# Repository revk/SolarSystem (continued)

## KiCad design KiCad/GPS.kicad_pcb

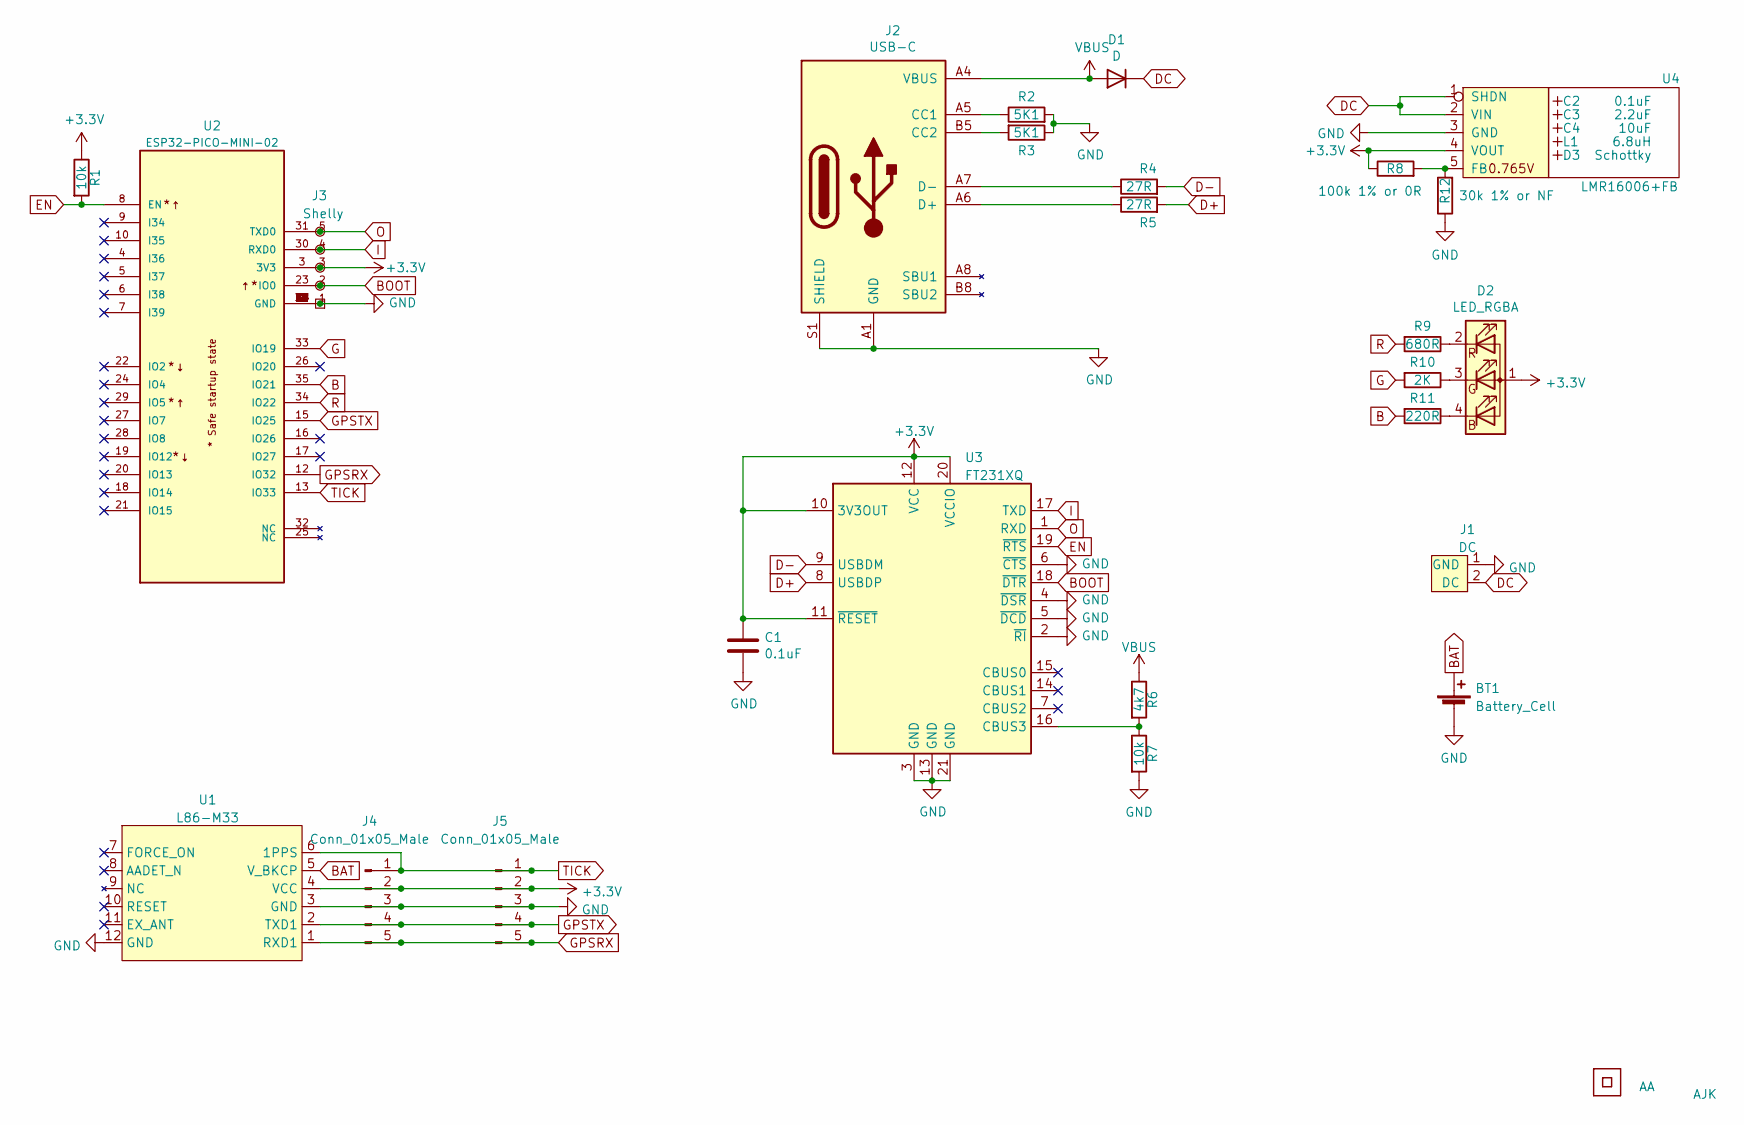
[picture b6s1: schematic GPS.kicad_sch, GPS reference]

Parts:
BT1: Battery_Cell; Battery-Holder-2032
C1: 0.1uF; C_0603
C2: 0.1uF; C_0603_
C3: 2.2uF; C_0805_
C4: 10uF; C_0805_
D1: D; D_1206
D2: LED_RGBA; LED-RGB-1.6x1.6
D3: Schottky; D_1206_; Part No CD1206-B2100
J1: DC; Molex_MiniSPOX_H2RA
J2: USB-C; USC16-TR
J3: Shelly
J4, J5: Conn_01x05_Male; PinHeader_1x05_P1.27mm_Vertical
L1: 6.8uH; L_4x4_; Part No TYA4020
Logo1: AA
Logo2: AJK
R1, R7: 10k; R_0603
R2, R3: 5K1; R_0603
R4, R5: 27R; R_0603
R6: 4k7; R_0603
R8: 100k 1% or 0R; R_0603
R9: 680R; R_0603
R10: 2K; R_0603
R11: 220R; R_0603
R12: 30k 1% or NF; R_0603
U1: L86-M33
U2: ESP32-PICO-MINI-02; PARTREV v1.0
U3: FT231XQ; QFN-20-1EP_4x4mm_P0.5mm_EP2.5x2.5mm
U4: LMR16006+FB; SOT-23-Thin-6-Reg; Part No LMR16006YQ3
U5: QR; QR-SS

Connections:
+3V3: C1.1, D2.1 (A), J3.3 (3V3), J4.2, J5.2, R1.1, R8.1, U1.4 (VCC), U2.3 (3V3), U3.10 (3V3OUT), U3.11 (~RESET), U3.12 (VCC), U3.20 (VCCIO), U4.4 (VOUT)
B: R11.2, U2.35 (IO21)
BAT: BT1.1 (+), U1.5 (V_BKCP)
BOOT: J3.2 (0), U2.23 (IO0), U3.18 (~DTR)
D+: R5.2, U3.8 (USBDP)
D-: R4.2, U3.9 (USBDM)
DC: D1.1 (K), J1.2 (DC), U4.1 (SHDN), U4.2 (VIN)
EN: R1.2, U2.8 (EN), U3.19 (~RTS)
G: R10.2, U2.33 (IO19)
GND: BT1.2 (-), C1.2, J1.1 (GND), J2.A1 (GND), J2.A12 (GND), J2.B1 (GND), J2.B12 (GND), J2.S1 (SHIELD), J3.1 (GND), J4.3, J5.3, R2.2, R3.1, R7.2, R12.1, U1.3 (GND), U1.12 (GND), U2.1 (GND), U2.2 (GND), U2.11 (GND), U2.14 (GND), U2.36 (GND), U2.37 (GND), U2.38 (GND), U2.39 (GND), U2.40 (GND), U2.41 (GND), U2.42 (GND), U2.43 (GND), U2.44 (GND), U2.45 (GND), U2.46 (GND), U2.47 (GND), U2.48 (GND), U2.49 (GND), U2.50 (GND), U2.51 (GND), U2.52 (GND), U2.53 (GND), U3.2 (~RI), U3.3 (GND), U3.4 (~DSR), U3.5 (~DCD), U3.6 (~CTS), U3.13 (GND), U3.21 (GND), U4.3 (GND)
GPSRX: J4.5, J5.5, U1.1 (RXD1), U2.12 (IO32)
GPSTX: J4.4, J5.4, U1.2 (TXD1), U2.15 (IO25)
I: J3.4 (Rx), U2.30 (RXD0), U3.17 (TXD)
unnamed: D2.2 (RK), R9.1
unnamed: D2.3 (GK), R10.1
unnamed: D2.4 (BK), R11.1
unnamed: J2.A5 (CC1), R2.1
unnamed: J2.A6 (D+), J2.B6 (D+), R5.1
unnamed: J2.A7 (D-), J2.B7 (D-), R4.1
unnamed: J2.B5 (CC2), R3.2
unnamed: R6.2, R7.1, U3.16 (CBUS3)
unnamed: R8.2, R12.2, U4.5 (FB)
O: J3.5 (Tx), U2.31 (TXD0), U3.1 (RXD)
R: R9.2, U2.34 (IO22)
TICK: J4.1, J5.1, U1.6 (1PPS), U2.13 (IO33)
VBUS: D1.2 (A), J2.A4 (VBUS), J2.A9 (VBUS), J2.B4 (VBUS), J2.B9 (VBUS), R6.1

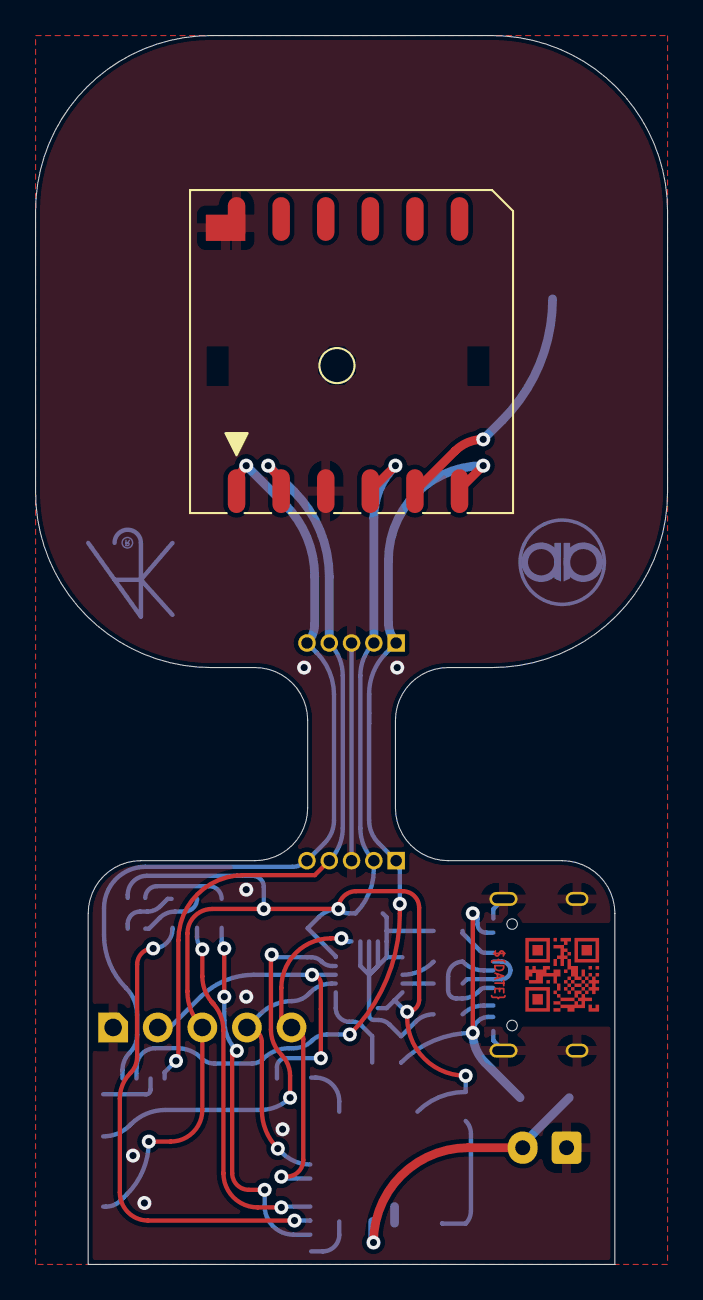
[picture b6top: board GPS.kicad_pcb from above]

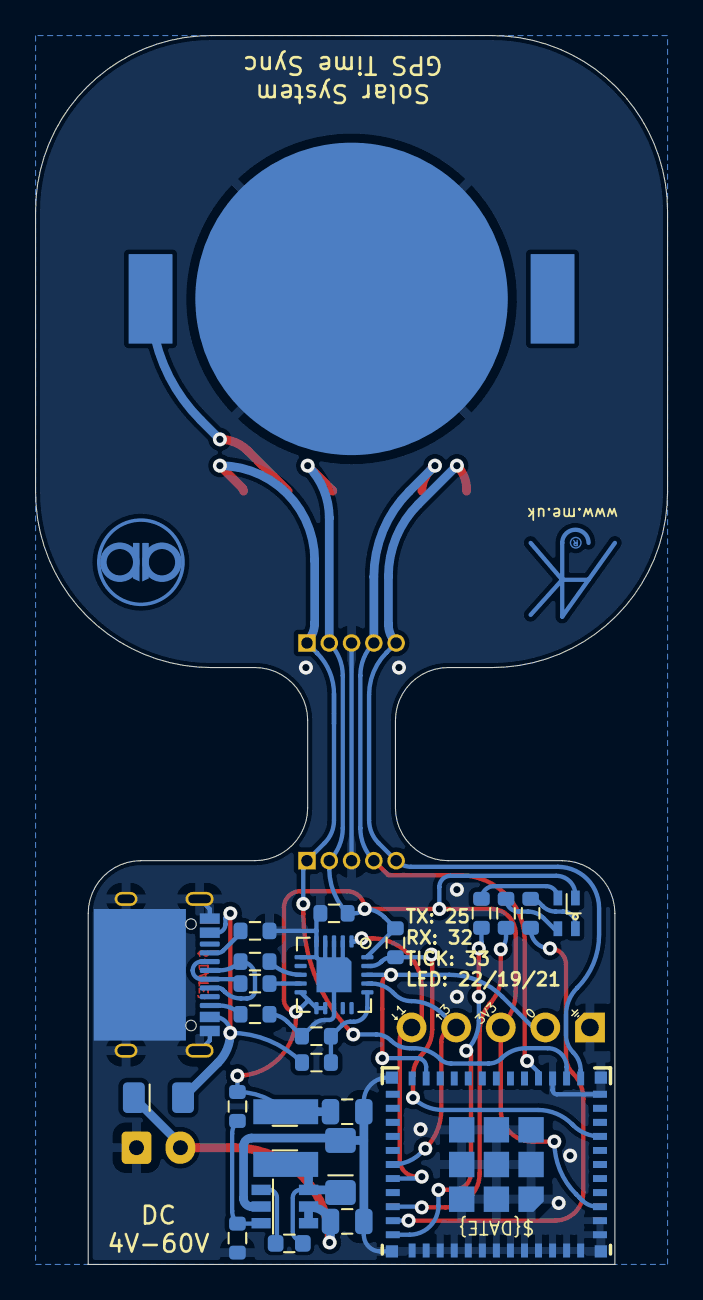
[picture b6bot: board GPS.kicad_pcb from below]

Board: 2 copper layers, 36.0 x 70.0 mm, 33 parts (29 on the bottom side), 26 nets.

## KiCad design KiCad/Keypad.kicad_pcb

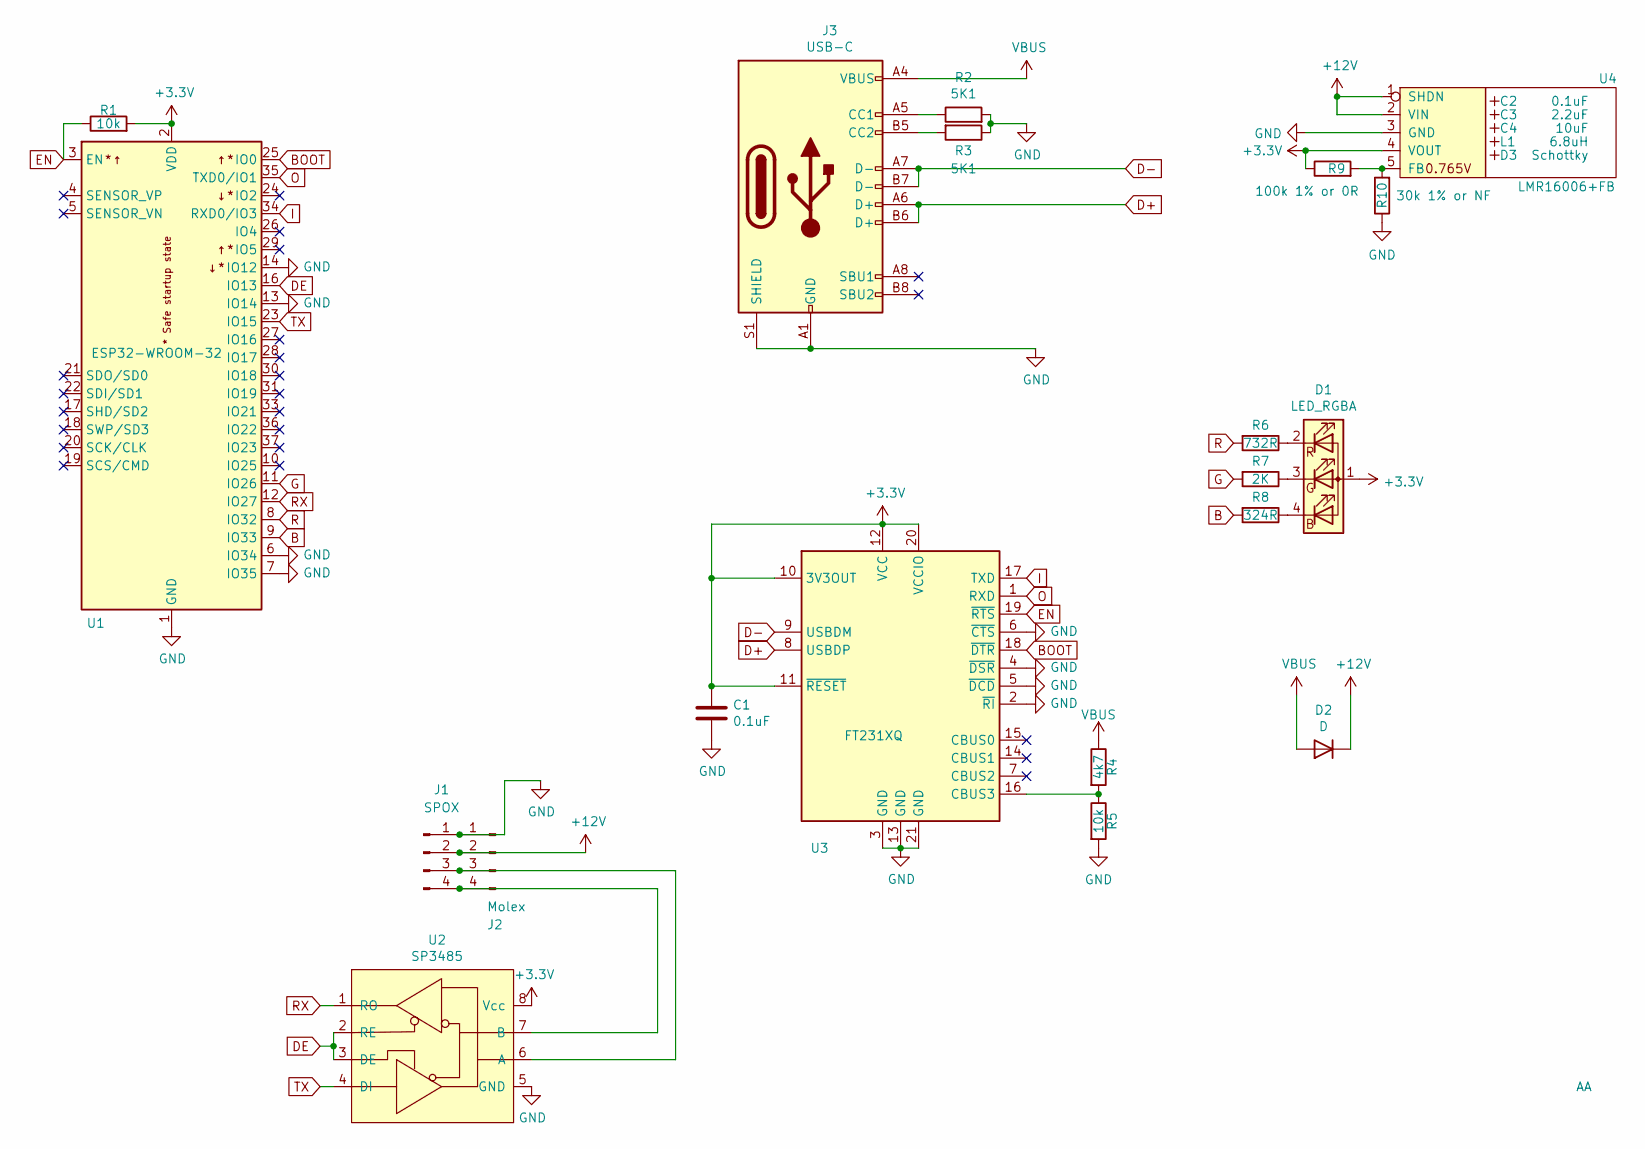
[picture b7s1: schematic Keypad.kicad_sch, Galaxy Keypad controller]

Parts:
C1: 0.1uF; C_0603
C2: 0.1uF; Hidden
C3: 2.2uF; Hidden
C4: 10uF; Hidden
D1: LED_RGBA; LED-RGB-1.6x1.6
D2: D; D_1206_3216Metric_Pad1.42x1.75mm_HandSolder
D3: Schottky; Hidden; Part No CD1206-B2100
J1: SPOX; Molex_MiniSPOX_H4RA
J2: Molex; PinHeader_1x04_P2.54mm_Vertical
J3: USB-C; USC16-TR-Round
L1: 6.8uH; Hidden; Part No TYA4020
Logo1: AA
R1, R5: 10k; R_0603
R2, R3: 5K1; R_0603
R4: 4k7; R_0603
R6: 732R; R_0603
R7: 2K; R_0603
R8: 324R; R_0603
R9: 100k 1% or 0R; R_0603
R10: 30k 1% or NF; R_0603
U1: ESP32-WROOM-32
U2: SP3485; SOIC-8_3.9x4.9mm_P1.27mm
U3: FT231XQ; QFN-20-1EP_4x4mm_P0.5mm_EP2.5x2.5mm
U4: LMR16006+FB; RegulatorBlockFB; Part No LMR16006YQ3

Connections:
+3V3: C1.1, D1.1 (A), R1.2, R9.1, U1.2 (VDD), U2.8 (Vcc), U3.10 (3V3OUT), U3.11 (~RESET), U3.12 (VCC), U3.20 (VCCIO), U4.4 (VOUT)
+12V: D2.1 (K), J1.2, J2.2, U4.1 (SHDN), U4.2 (VIN)
B: R8.2, U1.9 (IO33)
BOOT: U1.25 (IO0), U3.18 (~DTR)
D+: J3.A6 (D+), J3.B6 (D+), U3.8 (USBDP)
D-: J3.A7 (D-), J3.B7 (D-), U3.9 (USBDM)
DE: U1.16 (IO13), U2.2 (RE), U2.3 (DE)
EN: R1.1, U1.3 (EN), U3.19 (~RTS)
G: R7.2, U1.11 (IO26)
GND: C1.2, J1.1, J2.1, J3.A1 (GND), J3.A12 (GND), J3.B1 (GND), J3.B12 (GND), J3.S1 (SHIELD), R2.2, R3.1, R5.2, R10.1, U1.1 (GND), U1.6 (IO34), U1.7 (IO35), U1.13 (IO14), U1.14 (IO12), U1.15 (GND), U1.38 (GND), U1.39 (GND), U2.5 (GND), U3.2 (~RI), U3.3 (GND), U3.4 (~DSR), U3.5 (~DCD), U3.6 (~CTS), U3.13 (GND), U3.21 (GND), U4.3 (GND)
I: U1.34 (RXD0/IO3), U3.17 (TXD)
unnamed: D1.2 (RK), R6.1
unnamed: D1.3 (GK), R7.1
unnamed: D1.4 (BK), R8.1
unnamed: J1.3, J2.3, U2.6 (A)
unnamed: J1.4, J2.4, U2.7 (B)
unnamed: J3.A5 (CC1), R2.1
unnamed: J3.B5 (CC2), R3.2
unnamed: R4.2, R5.1, U3.16 (CBUS3)
unnamed: R9.2, R10.2, U4.5 (FB)
O: U1.35 (TXD0/IO1), U3.1 (RXD)
R: R6.2, U1.8 (IO32)
RX: U1.12 (IO27), U2.1 (RO)
TX: U1.23 (IO15), U2.4 (DI)
VBUS: D2.2 (A), J3.A4 (VBUS), J3.A9 (VBUS), J3.B4 (VBUS), J3.B9 (VBUS), R4.1

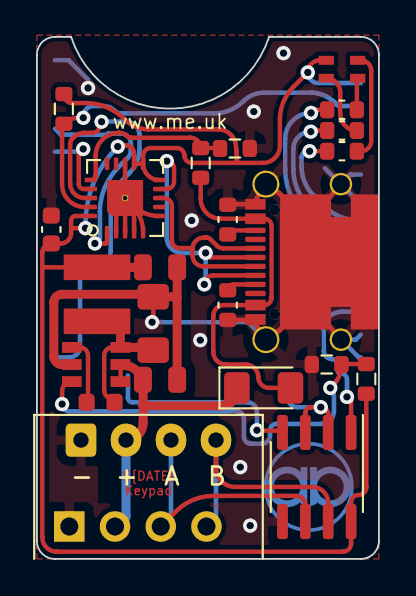
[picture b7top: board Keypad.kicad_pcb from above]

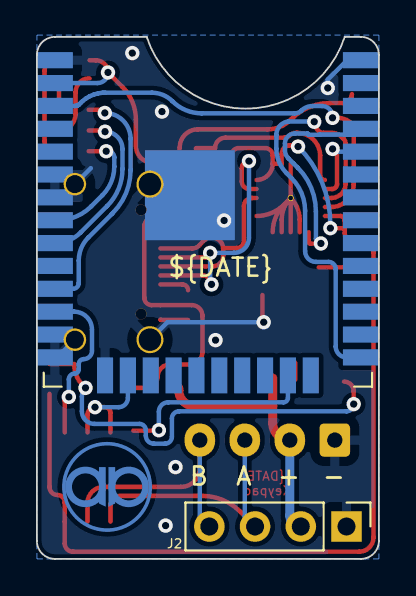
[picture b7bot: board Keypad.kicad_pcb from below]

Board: 2 copper layers, 19.0 x 29.0 mm, 26 parts (3 on the bottom side), 25 nets.
